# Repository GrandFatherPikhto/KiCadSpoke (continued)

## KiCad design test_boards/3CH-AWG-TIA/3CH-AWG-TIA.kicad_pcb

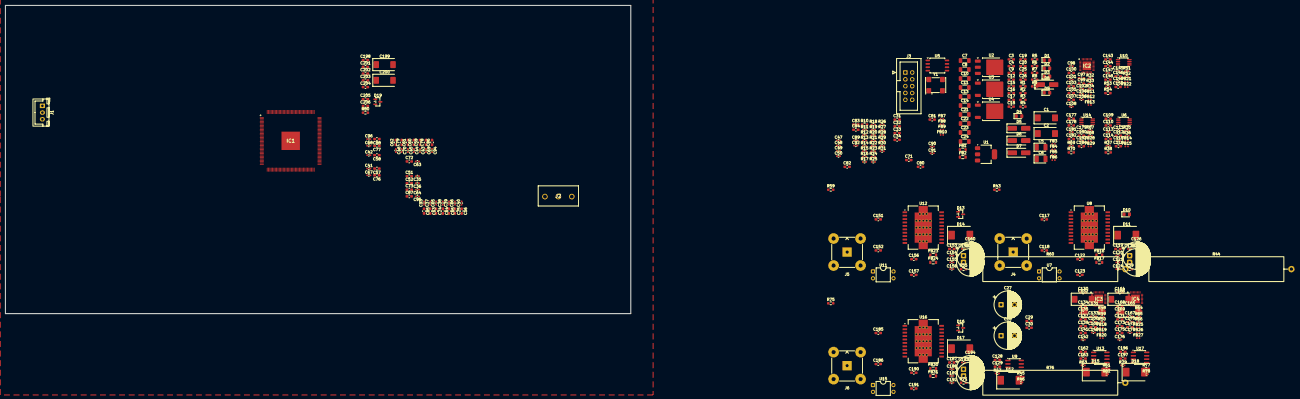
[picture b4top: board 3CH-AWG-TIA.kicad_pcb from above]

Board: 4 copper layers, 232.8 x 114.7 mm, 364 parts (0 on the bottom side), 183 nets, no tracks yet.

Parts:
C1, C2: TAJD107K016RNJ; CP_EIA-7343-20_Kemet-V_HandSolder
C3, C4, C9, C12, C15, C16, C17, C18, C19, C20, C25, C26, C110, C144, C178: 100 nF; C_0603_1608Metric_Pad1.08x0.95mm_HandSolder
C5, C6: TAJB476K010UNJ; CP_EIA-3528-12_Kemet-T_HandSolder
C7, C8, C10, C11, C13, C14, C21, C22: 1 uF; C_1206_3216Metric_Pad1.33x1.80mm_HandSolder
C23, C24: 10 uF; C_1206_3216Metric_Pad1.33x1.80mm_HandSolder
C27, C28, C126, C127, C160, C161, C194, C195: 470 uF; CP_Radial_D10.0mm_P5.00mm
C29, C30, C128, C129, C133, C134, C138, C162, C163, C167, C168, C172, C196, C197, C201, C202, C206: 100nF; C_0603_1608Metric_Pad1.08x0.95mm_HandSolder
C31, C32, C33, C34, C81, C82, C83, C84, C97, C99, C100, C103, C105, C107, C109, C112, C114, C116, C117, C118, C119, C122, C123, C137, C139, C141, C143, C146, C148, C150, C151, C152, C153, C156, C157, C171, C173, C175, C177, C180, C182, C184, C185, C186, C187, C190, C191, C205: 1uF; C_0603_1608Metric_Pad1.08x0.95mm_HandSolder
C35, C36, C37, C38, C39, C40, C41, C42, C43, C44, C45, C46, C47, C48, C49, C50, C63, C64, C65, C66, C67, C68, C69, C70, C89, C90, C91, C92, C93, C94, C95, C96, C98, C101, C102, C104, C106, C108, C111, C113, C115, C120, C121, C124, C125, C140, C142, C145, C147, C149, C154, C155, C158, C159, C174, C176, C179, C181, C183, C188, C189, C192, C193: 100 nF; C_0402_1005Metric_Pad0.74x0.62mm_HandSolder
C51, C52, C53, C54, C55, C56, C57, C58, C59, C60, C61, C62, C71, C72, C73, C74, C75, C76, C77, C78, C79, C80, C85, C86, C87, C88: 4.7 uF; C_0603_1608Metric_Pad1.08x0.95mm_HandSolder
C130, C164, C198: 1 nF; C_0603_1608Metric_Pad1.08x0.95mm_HandSolder
C131, C132, C165, C166, C199, C200: 22uF; CP_EIA-7343-20_Kemet-V
C135, C169, C203: 1.9 pF; C_0603_1608Metric_Pad1.08x0.95mm_HandSolder
C136, C170, C204: 22 pF; C_0603_1608Metric_Pad1.08x0.95mm_HandSolder
D1, D2, D3, D4, D9, D10: LED; D_0805_2012Metric_Pad1.15x1.40mm_HandSolder
D5, D6, D7, D8: D; D_SMA_Handsoldering
D11, D12, D14, D15, D17, D18: MBRS360BT3G; D_SMC
D13, D16, D19: BAT54S; SOT-23
FB1, FB2, FB16, FB17, FB23, FB24, FB30, FB31: BLM21PG121SN1D; L_0805_2012Metric
FB3, FB4, FB5, FB6, FB7, FB8, FB9, FB10, FB11, FB12, FB13, FB14, FB15, FB18, FB19, FB20, FB21, FB22, FB25, FB26, FB27, FB28, FB29: BLM15PD121SN1D; L_0402_1005Metric
IC1: 10CL006YE144C8G; QFP50P2200X2200X165-145N
IC2, IC3, IC4: AD9707BCPZ; QFN50P500X500X80-33N-D
J1: ±5V In; JST_XH_B3B-XH-A_1x03_P2.50mm_Vertical
J2: +-18V_PA; KF3013P
J3: CL_JTAG; IDC-Header_2x05_P2.54mm_Vertical
J4, J5, J6: Signal Out; BNC_TEConnectivity_1478035_Horizontal
R1, R2: 470; R_0603_1608Metric_Pad0.98x0.95mm_HandSolder
R3: 50; R_0603_1608Metric_Pad0.98x0.95mm_HandSolder
R4, R40, R56, R72: 330; R_0603_1608Metric_Pad0.98x0.95mm_HandSolder
R5, R6, R7, R8: 240; R_0603_1608Metric_Pad0.98x0.95mm_HandSolder
R9, R10: 220; R_0603_1608Metric_Pad0.98x0.95mm_HandSolder
R11: 1K; R_0402_1005Metric_Pad0.72x0.64mm_HandSolder
R12, R25, R26, R27, R30, R31, R32: 10K; R_0402_1005Metric_Pad0.72x0.64mm_HandSolder
R13, R28, R29: 4.7K; R_0402_1005Metric_Pad0.72x0.64mm_HandSolder
R14, R18, R19, R20, R21, R22, R23: 33; R_0402_1005Metric_Pad0.72x0.64mm_HandSolder
R15, R16, R17, R24: 2R2; R_0402_1005Metric_Pad0.72x0.64mm_HandSolder
R33, R34, R49, R50, R65, R66: 22; R_0402_1005Metric_Pad0.72x0.64mm_HandSolder
R35, R51, R67: 8.2K; R_0402_1005Metric_Pad0.72x0.64mm_HandSolder
R36, R37, R52, R53, R68, R69: 249; R_0402_1005Metric_Pad0.72x0.64mm_HandSolder
R38, R54, R70: 150R0; R_0603_1608Metric_Pad0.98x0.95mm_HandSolder
R39, R55, R71: 140R0; R_0603_1608Metric_Pad0.98x0.95mm_HandSolder
R41, R57, R73: 2K0; R_0603_1608Metric_Pad0.98x0.95mm_HandSolder
R42, R58, R74: 10K0; R_0603_1608Metric_Pad0.98x0.95mm_HandSolder
R43, R48, R59, R64, R75, R80: 10K; R_0603_1608Metric_Pad0.98x0.95mm_HandSolder
R44, R60, R76: BPR56 22R; R_Axial_Power_L50.0mm_W9.0mm_P55.88mm
R45, R61, R77: 2K10; R_0603_1608Metric_Pad0.98x0.95mm_HandSolder
R46, R62, R78: 560; R_0402_1005Metric_Pad0.72x0.64mm_HandSolder
R47, R63, R79: 10K0; R_0402_1005Metric_Pad0.72x0.64mm_HandSolder
U1: AMS1117-1.2; SOT-223-3_TabPin2
U2: AMS1117CD-3.3; TO-252-3_TabPin2
U3: LM317_TO-252; TO-252-2
U4: LM337_TO252; TO-252-2
U5: W25Q128JVS; SOIC-8_5.3x5.3mm_P1.27mm
U6, U10, U14: ADA4807-2ARM; MSOP-8_3x3mm_P0.65mm
U7, U11, U15: PC817; DIP-4_W7.62mm
U8, U12, U16: ADA4870ARRZ; HSOP-20-1EP_11.0x15.9mm_P1.27mm_SlugDown_ThermalVias
U9, U13, U17: LM311; SOIC-8_3.9x4.9mm_P1.27mm
Y1: SG-7050CAN; Oscillator_SMD_SeikoEpson_SG8002CA-4Pin_7.0x5.0mm

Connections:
+1V2: C13.1, C15.1, C31.1, C32.1, C47.1, C48.1, FB3.2, FB7.1, FB8.1, R3.2
+1V2_DIRTY: C5.1, C10.1, FB3.1, U1.2 (VO)
+1V2_VCCD_PLL: C82.1, C85.1, C86.1, C90.1, C93.1, C94.1, FB8.2, IC1.37 (VCCD_PLL1), IC1.109 (VCCD_PLL2)
+1V2_VCCINT: C63.1, C64.1, C65.1, C66.1, C67.1, C68.1, C69.1, C70.1, C71.1, C72.1, C73.1, C74.1, C75.1, C76.1, C77.1, C78.1, C79.1, C80.1, C81.1, C89.1, FB7.2, IC1.5 (VCCINT_1), IC1.29 (VCCINT_2), IC1.45 (VCCINT_3), IC1.61 (VCCINT_4), IC1.78 (VCCINT_5), IC1.102 (VCCINT_6), IC1.116 (VCCINT_7), IC1.134 (VCCINT_8)
+2V5: C21.1, C25.1, C33.1, C49.1, C118.1, C120.1, C152.1, C154.1, C186.1, C188.1, FB5.2, FB9.1, FB14.1, FB21.1, FB28.1, R10.2
+2V5_DIRTY: C18.1, D5.2 (A), D7.1 (K), FB5.1, R7.1, U3.2 (VO)
+2V5_VCCA: C83.1, C87.1, C88.1, C91.1, C95.1, C96.1, FB9.2, IC1.35 (VCCA1), IC1.96 (MSEL1), IC1.107 (VCCA2)
+3V3: C14.1, C16.1, C34.1, C50.1, C97.1, C98.1, C100.1, C102.1, C105.1, C106.1, C109.1, C111.1, C114.1, C115.1, C137.1, C138.1, C139.1, C140.1, C143.1, C145.1, C148.1, C149.1, C171.1, C172.1, C173.1, C174.1, C177.1, C179.1, C182.1, C183.1, C205.1, C206.1, D13.2 (K), D16.2 (K), D19.2 (K), FB4.2, FB10.1, FB11.1, FB12.1, FB13.1, FB18.1, FB19.1, FB20.1, FB25.1, FB26.1, FB27.1, R4.2, R15.1, R24.1, R48.1, R64.1, R80.1, U9.8 (V+), U13.8 (V+), U17.8 (V+)
+3V3_DIRTY: C6.1, C11.1, FB4.1, U2.2 (VO)
+3V3_FLASH: C103.1, C104.2, R16.2, R17.2, R24.2, U5.8 (VCC)
+3V3_OSCILL: C99.1, C101.2, R11.1, R15.2, Y1.4 (VCC)
+3V3_VCCIO: C35.1, C36.1, C37.1, C38.1, C39.1, C40.1, C41.1, C42.1, C43.1, C44.1, C45.1, C46.1, C51.1, C52.1, C53.1, C54.1, C55.1, C56.1, C57.1, C58.1, C59.1, C60.1, C61.1, C62.1, C84.1, C92.1, FB10.2, IC1.17 (VCCIO1), IC1.26 (VCCIO2), IC1.40 (VCCIO3_1), IC1.47 (VCCIO3_2), IC1.56 (VCCIO4_1), IC1.62 (VCCIO4_2), IC1.81 (VCCIO5), IC1.93 (VCCIO6), IC1.117 (VCCIO7_1), IC1.122 (VCCIO7_2), IC1.130 (VCCIO8_1), IC1.139 (VCCIO8_2), J3.4, R25.2, R26.2, R27.2, R28.2, R29.2, R30.2, R31.2, R32.2
+5V: C7.1, C9.1, C17.2, D5.1 (K), FB1.2, R1.2, U1.3 (VI), U2.3 (VI), U3.3 (VI)
+5V_DIRTY: C1.1, C3.1, FB1.1, J1.1
+18V_IN: C27.1, C29.1, C126.1, C128.1, C160.1, C162.1, C194.1, C196.1, FB16.1, FB23.1, FB30.1, J2.1
-2V5: C22.1, C26.1, C119.1, C121.1, C153.1, C155.1, C187.1, C189.1, FB6.2, FB15.1, FB22.1, FB29.1, R9.2
-2V5_DIRTY: C19.1, D6.2 (A), D8.1 (K), FB6.1, R8.2, U4.3 (VO)
-5V: C8.1, C12.1, C20.1, D6.1 (K), FB2.2, R2.2, U4.2 (VI)
-5V_DIRTY: C2.1, C4.1, FB2.1, J1.3
-18V_IN: C28.1, C30.1, C127.1, C129.1, C161.1, C163.1, C195.1, C197.1, FB17.1, FB24.1, FB31.1, J2.3
/Channel_0/DAC/+3V3_AVDD: C112.1, C113.1, FB12.2, IC2.18 (AVDD)
/Channel_0/DAC/+3V3_CLKVDD: C107.1, C108.1, FB11.2, IC2.11 (CLKVDD)
/Channel_0/DAC/+3V3_DVDD: C116.1, C117.1, FB13.2, IC2.3 (DVDD)
/Channel_0/DAC/DAC_FS_ADJ: IC2.24 (FS_ADJ), R35.1
/Channel_0/DAC/DAC_OUT_N: IC2.20 (IOUTB), R34.1
/Channel_0/DAC/DAC_OUT_P: IC2.21 (IOUTA), R33.1
/Channel_0/DAC/DAC_REFIO: C110.1, IC2.23 (REFIO)
/Channel_0/DAC_CLK_N: IC2.13 (CLK-), R19.2
/Channel_0/DAC_CLK_P: IC2.12 (CLK+), R18.2
/Channel_0/DAC_DB0: IC1.51 (IO_24), IC2.9 (DB0_(LSB))
/Channel_0/DAC_DB1: IC1.52 (IO_25), IC2.8 (DB1)
/Channel_0/DAC_DB2: IC1.53 (IO_26), IC2.7 (DB2)
/Channel_0/DAC_DB3: IC1.54 (IO_27), IC2.6 (DB3)
/Channel_0/DAC_DB4: IC1.55 (IO_28), IC2.5 (DB4)
/Channel_0/DAC_DB5: IC1.58 (IO_29), IC2.4 (DB5)
/Channel_0/DAC_DB6: IC1.59 (IO_30), IC2.2 (DB6)
/Channel_0/DAC_DB7: IC1.60 (IO_31), IC2.1 (DB7)
/Channel_0/DAC_DB8: IC1.65 (IO_32), IC2.32 (DB8)
/Channel_0/DAC_DB9: IC1.66 (IO_33), IC2.31 (DB9)
/Channel_0/DAC_DB10: IC1.67 (IO_34), IC2.30 (DB10)
/Channel_0/DAC_DB11: IC1.68 (IO_35), IC2.29 (DB11)
/Channel_0/DAC_DB12: IC1.69 (IO_36), IC2.28 (DB12)
/Channel_0/DAC_DB13: IC1.70 (IO_37), IC2.27 (DB13_(MSB))
/Channel_0/OpAmp/+2V5_OA: C122.1, C124.1, FB14.2, U6.8 (V+)
/Channel_0/OpAmp/-2V5_OA: C123.1, C125.1, FB15.2, U6.4 (V-)
/Channel_0/OpAmp/OA_IN_N: R34.2, R37.1, U6.6 (-)
/Channel_0/OpAmp/OA_IN_P: R33.2, R36.1, U6.2 (-)
/Channel_0/OpAmp/OA_OUT_N: R37.2, R38.1, U6.7
/Channel_0/OpAmp/OA_OUT_P: R36.2, R39.1, U6.1
/Channel_0/OpAmp/PA_IN_P: R39.2, U8.6 (+)
/Channel_0/PA_EN: IC1.38 (IO_16), R40.2
/Channel_0/Power Amplifier Sheet/+18V_PA: C131.1, C133.1, D11.1 (K), FB16.2, U8.1 (V+), U8.18 (V+), U8.19 (V+), U8.20 (V+)
/Channel_0/Power Amplifier Sheet/-18V_PA: C130.2, C132.1, C134.1, D12.2 (A), FB17.2, R41.1, R46.2, U7.3, U8.10 (V-), U8.11 (V-), U8.12 (V-), U8.13 (V-), U9.4 (V-)
/Channel_0/Power Amplifier Sheet/PA_EN_IN: R40.1, U7.1
/Channel_0/Power Amplifier Sheet/PA_IN_N: C135.1, R38.2, R45.1, U8.7 (-)
/Channel_0/Power Amplifier Sheet/PA_ON: C130.1, R43.2, U7.4, U8.4 (~ON)
/Channel_0/Power Amplifier Sheet/PA_SD: R41.2, R42.1, R43.1, U8.3 (~SD)
/Channel_0/Power Amplifier Sheet/PA_SIGNAL: C135.2, D11.2 (A), D12.1 (K), R44.1, R45.2, U8.8, U8.14, U8.15, U8.16, U8.17
/Channel_0/Power Amplifier Sheet/PA_SIGNAL_OUT: C136.1, J4.1 (In), R44.2
/Channel_0/Power Amplifier Sheet/PA_TFL: U8.2 (TFL), U9.2 (+)
/Channel_0/TFL/CL_TFL_SIGNAL: D13.3 (COM), IC1.31 (IO_12), R48.2, U9.7
/Channel_0/TFL/PA_TFL_V_REF: R46.1, R47.2, U9.3 (-)
/Channel_1/DAC/+3V3_AVDD: C146.1, C147.1, FB19.2, IC3.18 (AVDD)
/Channel_1/DAC/+3V3_CLKVDD: C141.1, C142.1, FB18.2, IC3.11 (CLKVDD)
/Channel_1/DAC/+3V3_DVDD: C150.1, C151.1, FB20.2, IC3.3 (DVDD)
/Channel_1/DAC/DAC_FS_ADJ: IC3.24 (FS_ADJ), R51.1
/Channel_1/DAC/DAC_OUT_N: IC3.20 (IOUTB), R50.1
/Channel_1/DAC/DAC_OUT_P: IC3.21 (IOUTA), R49.1
/Channel_1/DAC/DAC_REFIO: C144.1, IC3.23 (REFIO)
/Channel_1/DAC_CLK_N: IC3.13 (CLK-), R21.2
/Channel_1/DAC_CLK_P: IC3.12 (CLK+), R20.2
/Channel_1/DAC_DB0: IC1.75 (IO_42), IC3.9 (DB0_(LSB))
/Channel_1/DAC_DB1: IC1.76 (IO_43), IC3.8 (DB1)
/Channel_1/DAC_DB2: IC1.77 (IO_44), IC3.7 (DB2)
/Channel_1/DAC_DB3: IC1.80 (IO_45), IC3.6 (DB3)
/Channel_1/DAC_DB4: IC1.83 (IO_46), IC3.5 (DB4)
/Channel_1/DAC_DB5: IC1.84 (IO_47), IC3.4 (DB5)
/Channel_1/DAC_DB6: IC1.85 (IO_48), IC3.2 (DB6)
/Channel_1/DAC_DB7: IC1.86 (IO_49), IC3.1 (DB7)
/Channel_1/DAC_DB8: IC1.87 (IO_50), IC3.32 (DB8)
/Channel_1/DAC_DB9: IC1.98 (IO_51), IC3.31 (DB9)
/Channel_1/DAC_DB10: IC1.99 (IO_52), IC3.30 (DB10)
/Channel_1/DAC_DB11: IC1.100 (IO_53), IC3.29 (DB11)
/Channel_1/DAC_DB12: IC1.101 (IO_54), IC3.28 (DB12)
/Channel_1/DAC_DB13: IC1.103 (IO_55), IC3.27 (DB13_(MSB))
/Channel_1/OpAmp/+2V5_OA: C156.1, C158.1, FB21.2, U10.8 (V+)
/Channel_1/OpAmp/-2V5_OA: C157.1, C159.1, FB22.2, U10.4 (V-)
/Channel_1/OpAmp/OA_IN_N: R50.2, R53.1, U10.6 (-)
/Channel_1/OpAmp/OA_IN_P: R49.2, R52.1, U10.2 (-)
/Channel_1/OpAmp/OA_OUT_N: R53.2, R54.1, U10.7
/Channel_1/OpAmp/OA_OUT_P: R52.2, R55.1, U10.1
/Channel_1/OpAmp/PA_IN_P: R55.2, U12.6 (+)
/Channel_1/PA_EN: IC1.39 (IO_17), R56.2
/Channel_1/Power Amplifier Sheet/+18V_PA: C165.1, C167.1, D14.1 (K), FB23.2, U12.1 (V+), U12.18 (V+), U12.19 (V+), U12.20 (V+)
/Channel_1/Power Amplifier Sheet/-18V_PA: C164.2, C166.1, C168.1, D15.2 (A), FB24.2, R57.1, R62.2, U11.3, U12.10 (V-), U12.11 (V-), U12.12 (V-), U12.13 (V-), U13.4 (V-)
/Channel_1/Power Amplifier Sheet/PA_EN_IN: R56.1, U11.1
/Channel_1/Power Amplifier Sheet/PA_IN_N: C169.1, R54.2, R61.1, U12.7 (-)
/Channel_1/Power Amplifier Sheet/PA_ON: C164.1, R59.2, U11.4, U12.4 (~ON)
/Channel_1/Power Amplifier Sheet/PA_SD: R57.2, R58.1, R59.1, U12.3 (~SD)
/Channel_1/Power Amplifier Sheet/PA_SIGNAL: C169.2, D14.2 (A), D15.1 (K), R60.1, R61.2, U12.8, U12.14, U12.15, U12.16, U12.17
/Channel_1/Power Amplifier Sheet/PA_SIGNAL_OUT: C170.1, J5.1 (In), R60.2
/Channel_1/Power Amplifier Sheet/PA_TFL: U12.2 (TFL), U13.2 (+)
/Channel_1/TFL/CL_TFL_SIGNAL: D16.3 (COM), IC1.32 (IO_13), R64.2, U13.7
/Channel_1/TFL/PA_TFL_V_REF: R62.1, R63.2, U13.3 (-)
/Channel_2/DAC/+3V3_AVDD: C180.1, C181.1, FB26.2, IC4.18 (AVDD)
/Channel_2/DAC/+3V3_CLKVDD: C175.1, C176.1, FB25.2, IC4.11 (CLKVDD)
/Channel_2/DAC/+3V3_DVDD: C184.1, C185.1, FB27.2, IC4.3 (DVDD)
/Channel_2/DAC/DAC_FS_ADJ: IC4.24 (FS_ADJ), R67.1
/Channel_2/DAC/DAC_OUT_N: IC4.20 (IOUTB), R66.1
/Channel_2/DAC/DAC_OUT_P: IC4.21 (IOUTA), R65.1
/Channel_2/DAC/DAC_REFIO: C178.1, IC4.23 (REFIO)
/Channel_2/DAC_CLK_N: IC4.13 (CLK-), R23.2
/Channel_2/DAC_CLK_P: IC4.12 (CLK+), R22.2
/Channel_2/DAC_DB0: IC1.113 (IO_60), IC4.9 (DB0_(LSB))
/Channel_2/DAC_DB1: IC1.114 (IO_61), IC4.8 (DB1)
/Channel_2/DAC_DB2: IC1.115 (IO_62), IC4.7 (DB2)
/Channel_2/DAC_DB3: IC1.119 (IO_63), IC4.6 (DB3)
/Channel_2/DAC_DB4: IC1.120 (IO_64), IC4.5 (DB4)
/Channel_2/DAC_DB5: IC1.121 (IO_65), IC4.4 (DB5)
/Channel_2/DAC_DB6: IC1.124 (IO_66), IC4.2 (DB6)
/Channel_2/DAC_DB7: IC1.125 (IO_67), IC4.1 (DB7)
/Channel_2/DAC_DB8: IC1.126 (IO_68), IC4.32 (DB8)
/Channel_2/DAC_DB9: IC1.127 (IO_69), IC4.31 (DB9)
/Channel_2/DAC_DB10: IC1.128 (IO_70), IC4.30 (DB10)
/Channel_2/DAC_DB11: IC1.129 (IO_71), IC4.29 (DB11)
/Channel_2/DAC_DB12: IC1.132 (IO_72), IC4.28 (DB12)
/Channel_2/DAC_DB13: IC1.133 (IO_73), IC4.27 (DB13_(MSB))
/Channel_2/OpAmp/+2V5_OA: C190.1, C192.1, FB28.2, U14.8 (V+)
/Channel_2/OpAmp/-2V5_OA: C191.1, C193.1, FB29.2, U14.4 (V-)
/Channel_2/OpAmp/OA_IN_N: R66.2, R69.1, U14.6 (-)
/Channel_2/OpAmp/OA_IN_P: R65.2, R68.1, U14.2 (-)
/Channel_2/OpAmp/OA_OUT_N: R69.2, R70.1, U14.7
/Channel_2/OpAmp/OA_OUT_P: R68.2, R71.1, U14.1
/Channel_2/OpAmp/PA_IN_P: R71.2, U16.6 (+)
/Channel_2/PA_EN: IC1.42 (IO_18), R72.2
/Channel_2/Power Amplifier Sheet/+18V_PA: C199.1, C201.1, D17.1 (K), FB30.2, U16.1 (V+), U16.18 (V+), U16.19 (V+), U16.20 (V+)
/Channel_2/Power Amplifier Sheet/-18V_PA: C198.2, C200.1, C202.1, D18.2 (A), FB31.2, R73.1, R78.2, U15.3, U16.10 (V-), U16.11 (V-), U16.12 (V-), U16.13 (V-), U17.4 (V-)
/Channel_2/Power Amplifier Sheet/PA_EN_IN: R72.1, U15.1
/Channel_2/Power Amplifier Sheet/PA_IN_N: C203.1, R70.2, R77.1, U16.7 (-)
/Channel_2/Power Amplifier Sheet/PA_ON: C198.1, R75.2, U15.4, U16.4 (~ON)
/Channel_2/Power Amplifier Sheet/PA_SD: R73.2, R74.1, R75.1, U16.3 (~SD)
/Channel_2/Power Amplifier Sheet/PA_SIGNAL: C203.2, D17.2 (A), D18.1 (K), R76.1, R77.2, U16.8, U16.14, U16.15, U16.16, U16.17
/Channel_2/Power Amplifier Sheet/PA_SIGNAL_OUT: C204.1, J6.1 (In), R76.2
/Channel_2/Power Amplifier Sheet/PA_TFL: U16.2 (TFL), U17.2 (+)
/Channel_2/TFL/CL_TFL_SIGNAL: D19.3 (COM), IC1.33 (IO_14), R80.2, U17.7
/Channel_2/TFL/PA_TFL_V_REF: R78.1, R79.2, U17.3 (-)
/FPGA/CL_ASDO: IC1.6 (IO_4), U5.5 (DI/IO_{0})
/FPGA/CL_CLK_0: R14.1, Y1.3 (OUT)
/FPGA/CL_CLK_0_IN: IC1.22 (CLK0), R14.2
/FPGA/CL_CLK_ON: R11.2, Y1.1 (~ST)
/FPGA/CL_CONFIG_DONE: IC1.92 (CONF_DONE), R25.1
/FPGA/CL_DATA0: IC1.13 (IO_10), U5.2 (DO/IO_{1})
/FPGA/CL_DCLK: IC1.12 (IO_9), U5.6 (CLK)
/FPGA/CL_NCONFIG: IC1.14 (NCONFIG), R27.1
/FPGA/CL_NCSO: IC1.8 (IO_6), U5.1 (~CS)
/FPGA/CL_NSTATUS: IC1.9 (NSTATUS), R26.1
/FPGA/CL_TCK: IC1.16 (TCK), J3.1, R13.1
/FPGA/CL_TDI: IC1.15 (TDI), J3.9, R29.1
/FPGA/CL_TDO: IC1.20 (TDO), J3.3
/FPGA/CL_TMS: IC1.18 (TMS), J3.5, R28.1
/FPGA/DAC0_CLK_OUT_N: IC1.49 (IO_22), R19.1
/FPGA/DAC0_CLK_OUT_P: IC1.50 (IO_23), R18.1
/FPGA/DAC0_SPI_CS: IC1.7 (IO_5), IC2.25 (SLEEP/CSB), R30.1
/FPGA/DAC1_CLK_OUT_N: IC1.73 (IO_40), R21.1
/FPGA/DAC1_CLK_OUT_P: IC1.74 (IO_41), R20.1
/FPGA/DAC1_SPI_CS: IC1.10 (IO_7), IC3.25 (SLEEP/CSB), R31.1
/FPGA/DAC2_CLK_OUT_N: IC1.111 (IO_58), R23.1
/FPGA/DAC2_CLK_OUT_P: IC1.112 (IO_59), R22.1
/FPGA/DAC2_SPI_CS: IC1.11 (IO_8), IC4.25 (SLEEP/CSB), R32.1
/FPGA/FL_HOLD: R16.1, U5.7 (~HOLD/~RESET/IO_{3})
/FPGA/FL_WP: R17.1, U5.3 (~WP/IO_{2})
/Power/+1V2_LED: D3.2 (A), R3.1
/Power/+2V5_ADJ: C23.1, D7.2 (A), R5.1, R7.2, U3.1 (ADJ)
/Power/+2V5_LED: D10.2 (A), R10.1
/Power/+3V3_LED: D4.2 (A), R4.1
/Power/+5V_LED: D1.2 (A), R1.1
/Power/-2V5_ADJ: C24.2, D8.2 (A), R6.2, R8.1, U4.1 (ADJ)
/Power/-2V5_LED: D9.2 (A), R9.1
/Power/-5V_LED: D2.2 (A), R2.1
DAC_SPI_RESET: IC1.3 (IO_3), IC2.17 (PIN/SPI/RESET), IC3.17 (PIN/SPI/RESET), IC4.17 (PIN/SPI/RESET), R12.1
DAC_SPI_SCK: IC1.1 (IO_1), IC2.15 (CMODE/SCLK), IC3.15 (CMODE/SCLK), IC4.15 (CMODE/SCLK)
DAC_SPI_SDIO: IC1.2 (IO_2), IC2.16 (MODE/SDIO), IC3.16 (MODE/SDIO), IC4.16 (MODE/SDIO)
GND: C1.2, C2.2, C3.2, C4.2, C5.2, C6.2, C7.2, C8.2, C9.2, C10.2, C11.2, C12.2, C13.2, C14.2, C15.2, C16.2, C17.1, C18.2, C19.2, C20.2, C21.2, C22.2, C23.2, C24.1, C25.2, C26.2, C27.2, C28.2, C29.2, C30.2, C31.2, C32.2, C33.2, C34.2, C35.2, C36.2, C37.2, C38.2, C39.2, C40.2, C41.2, C42.2, C43.2, C44.2, C45.2, C46.2, C47.2, C48.2, C49.2, C50.2, C51.2, C52.2, C53.2, C54.2, C55.2, C56.2, C57.2, C58.2, C59.2, C60.2, C61.2, C62.2, C63.2, C64.2, C65.2, C66.2, C67.2, C68.2, C69.2, C70.2, C71.2, C72.2, C73.2, C74.2, C75.2, C76.2, C77.2, C78.2, C79.2, C80.2, C81.2, C82.2, C83.2, C84.2, C85.2, C86.2, C87.2, C88.2, C89.2, C90.2, C91.2, C92.2, C93.2, C94.2, C95.2, C96.2, C97.2, C98.2, C99.2, C100.2, C101.1, C102.2, C103.2, C104.1, C105.2, C106.2, C107.2, C108.2, C109.2, C110.2, C111.2, C112.2, C113.2, C114.2, C115.2, C116.2, C117.2, C118.2, C119.2, C120.2, C121.2, C122.2, C123.2, C124.2, C125.2, C126.2, C127.2, C128.2, C129.2, C131.2, C132.2, C133.2, C134.2, C136.2, C137.2, C138.2, C139.2, C140.2, C141.2, C142.2, C143.2, C144.2, C145.2, C146.2, C147.2, C148.2, C149.2, C150.2, C151.2, C152.2, C153.2, C154.2, C155.2, C156.2, C157.2, C158.2, C159.2, C160.2, C161.2, C162.2, C163.2, C165.2, C166.2, C167.2, C168.2, C170.2, C171.2, C172.2, C173.2, C174.2, C175.2, C176.2, C177.2, C178.2, C179.2, C180.2, C181.2, C182.2, C183.2, C184.2, C185.2, C186.2, C187.2, C188.2, C189.2, C190.2, C191.2, C192.2, C193.2, C194.2, C195.2, C196.2, C197.2, C199.2, C200.2, C201.2, C202.2, C204.2, C205.2, C206.2, D1.1 (K), D2.1 (K), D3.1 (K), D4.1 (K), D9.1 (K), D10.1 (K), D13.1 (A), D16.1 (A), D19.1 (A), IC1.4 (GND_1), IC1.19 (GND_2), IC1.21 (NCE), IC1.27 (GND_3), IC1.30 (GND_4), IC1.36 (GNDA1), IC1.41 (GND_5), IC1.48 (GND_6), IC1.57 (GND_7), IC1.63 (GND_8), IC1.64 (GND_9), IC1.79 (GND_10), IC1.82 (GND_11), IC1.94 (MSEL0), IC1.95 (GND_12), IC1.97 (MSEL2), IC1.104 (GND_13), IC1.108 (GNDA2), IC1.110 (GND_14), IC1.118 (GND_15), IC1.123 (GND_16), IC1.131 (GND_17), IC1.140 (GND_18), IC1.145 (EP_(GND)), IC2.10 (DCOM_1), IC2.14 (CLKCOM), IC2.19 (OTCM), IC2.22 (ACOM), IC2.26 (DCOM_2), IC2.33 (EP), IC3.10 (DCOM_1), IC3.14 (CLKCOM), IC3.19 (OTCM), IC3.22 (ACOM), IC3.26 (DCOM_2), IC3.33 (EP), IC4.10 (DCOM_1), IC4.14 (CLKCOM), IC4.19 (OTCM), IC4.22 (ACOM), IC4.26 (DCOM_2), IC4.33 (EP), J1.2, J2.2, J3.2, J3.10, J4.2 (Ext), J5.2 (Ext), J6.2 (Ext), R5.2, R6.1, R12.2, R13.2, R35.2, R42.2, R47.1, R51.2, R58.2, R63.1, R67.2, R74.2, R79.1, U1.1 (GND), U2.1 (GND), U5.4 (GND), U6.3 (+), U6.5 (+), U7.2, U8.21 (PAD), U9.1 (GND), U10.3 (+), U10.5 (+), U11.2, U12.21 (PAD), U13.1 (GND), U14.3 (+), U14.5 (+), U15.2, U16.21 (PAD), U17.1 (GND), Y1.2 (GND)
